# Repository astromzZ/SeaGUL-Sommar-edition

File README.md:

# Seagul - Chalmers undervattensglidare

This repository is for Chalmers underwater glider SEAgul. Here you will find code, instructions and construction files for the glider.

Before handling the glider, make sure to read thorugh the manual. 

The most recent CAD files can be found [here](https://drive.google.com/drive/folders/1H2lXxEGizccBVgk5y8HHm3Ga0hIDHSA2?usp=drive_link).

Contact information:

Oskar Andersson - Oskar.simon.andersson@gmail.com (Programming, CAD)

Peo Gradin - peo.gradin@live.se (Electronics, Programming)

Joel Janson - joeljanson19@gmail.com (Hardware)

Cevin Åström - cevinastrom87@gmail.com (Programming)

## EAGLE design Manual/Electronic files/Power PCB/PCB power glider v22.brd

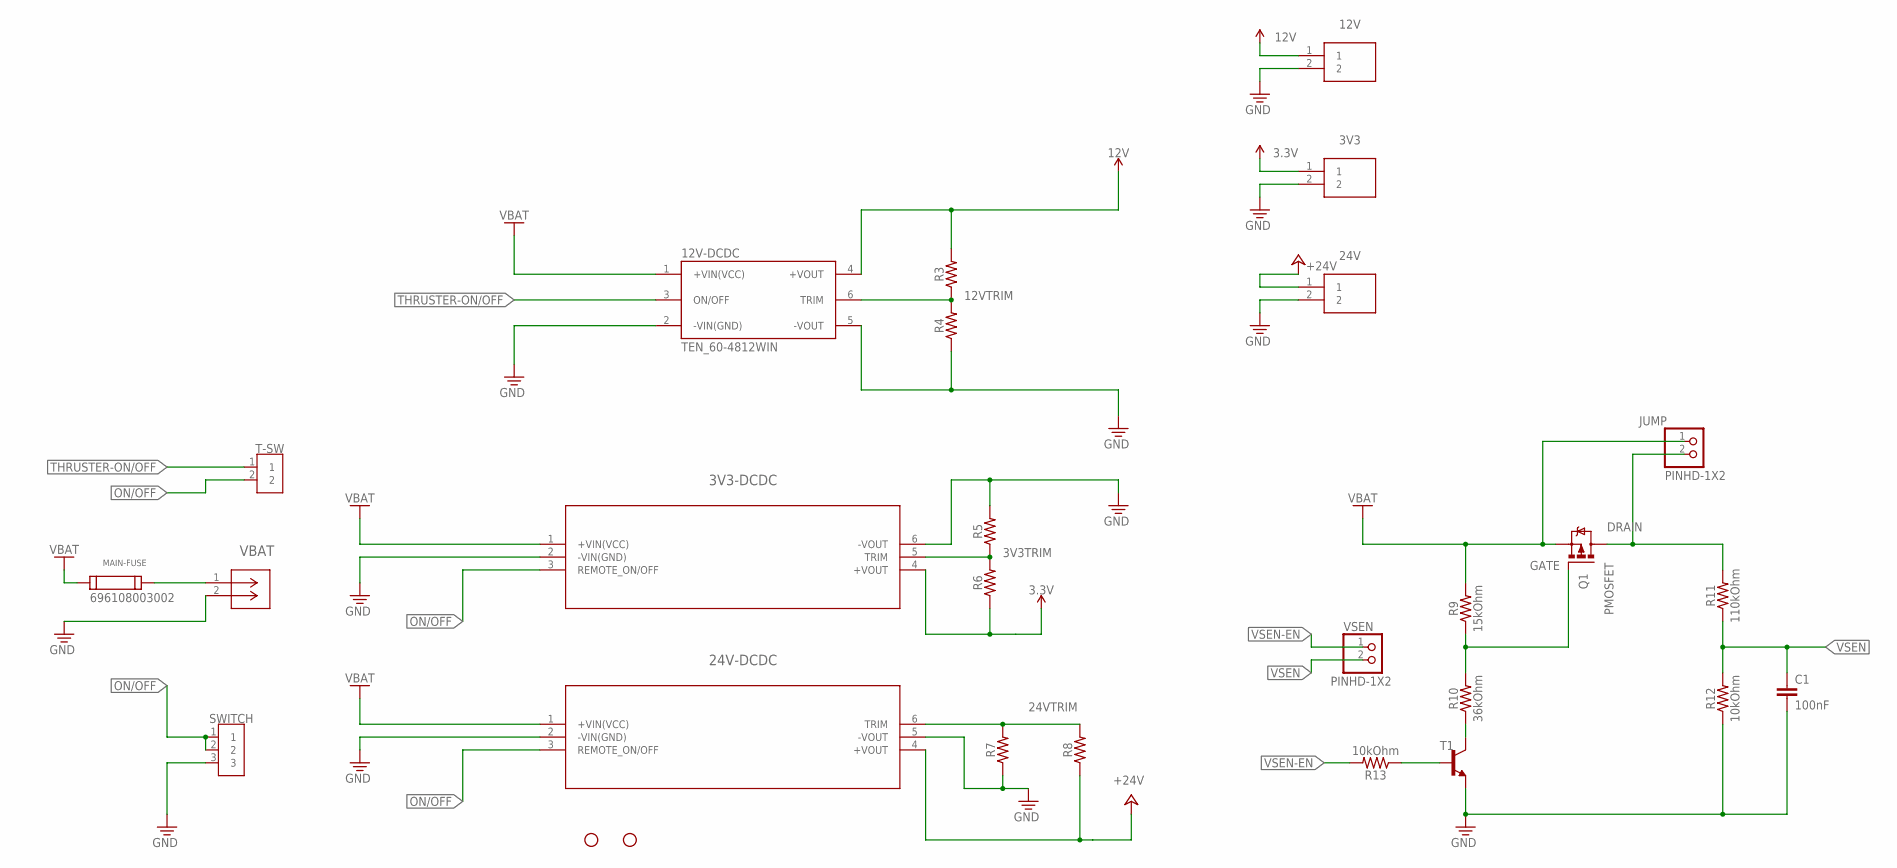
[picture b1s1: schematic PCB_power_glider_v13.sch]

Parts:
3V3, 12V, 24V: CTBP0508_2; CTBP05082
3V3-DCDC: THN_20-4810WIRTHN_20WIR_SINGLE_TRP; THN_20WIR_SINGLE_TRP
12V-DCDC: TEN_60-4812WIN; CONV_TEN_60-4812WIN
24V-DCDC: TEN_60-4815WINTEN_60WIN_TRP; TEN_60WIN_TRP
C1: 100nF; 0603
H1, H4: STAND-OFFTIGHT; STAND-OFF-TIGHT
JUMP: PINHD-1X2; 1X02
MAIN-FUSE: 696108003002
Q1: PMOSFET; SOT23
R3, R4, R5, R6, R7, R8: 0603
R9: 15kOhm; 0603
R10: 36kOhm; 0603
R11: 110kOhm; 0603
R12, R13: 10kOhm; 0603
SWITCH: 2828XX-3282834-3; TERMBLK_254-3N
T1: -NPN-SOT23-EBC; SOT23-EBC
T-SW: 2828XX-2282834-2; TERMBLK_254-2N
VBAT: NC6-P107-02CONN2_1437664-4_TEC; CONN2_1437664-4_TEC
VSEN: PINHD-1X2; 1X02

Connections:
3.3V: 3V3.1, 3V3-DCDC.4 (+VOUT), R6.1
3V3TRIM: 3V3-DCDC.5 (TRIM), R5.1, R6.2
12V: 12V.1, 12V-DCDC.4 (+VOUT), R3.2
12VTRIM: 12V-DCDC.6 (TRIM), R3.1, R4.2
24VTRIM: 24V-DCDC.6 (TRIM), R7.2, R8.2
+24V: 24V.1, 24V-DCDC.4 (+VOUT), R8.1
DRAIN: JUMP.2, Q1.3 (D), R11.2
GATE: Q1.1 (G), R9.1, R10.2
GND: 3V3.2, 3V3-DCDC.2 (-VIN(GND)), 3V3-DCDC.6 (-VOUT), 12V.2, 12V-DCDC.2 (-VIN(GND)), 12V-DCDC.5 (-VOUT), 24V.2, 24V-DCDC.2 (-VIN(GND)), 24V-DCDC.5 (-VOUT), C1.2, R4.1, R5.2, R7.1, R12.1, SWITCH.3, T1.E, VBAT.2
unnamed: MAIN-FUSE.2, VBAT.1
unnamed: R10.1, T1.C
unnamed: R13.1, T1.B
ON/OFF: 3V3-DCDC.3 (REMOTE_ON/OFF), 24V-DCDC.3 (REMOTE_ON/OFF), SWITCH.1, SWITCH.2, T-SW.2
THRUSTER-ON/OFF: 12V-DCDC.3 (ON/OFF), T-SW.1
VBAT: 3V3-DCDC.1 (+VIN(VCC)), 12V-DCDC.1 (+VIN(VCC)), 24V-DCDC.1 (+VIN(VCC)), JUMP.1, MAIN-FUSE.1, Q1.2 (S), R9.2
VSEN: C1.1, R11.1, R12.2, VSEN.2
VSEN-EN: R13.2, VSEN.1

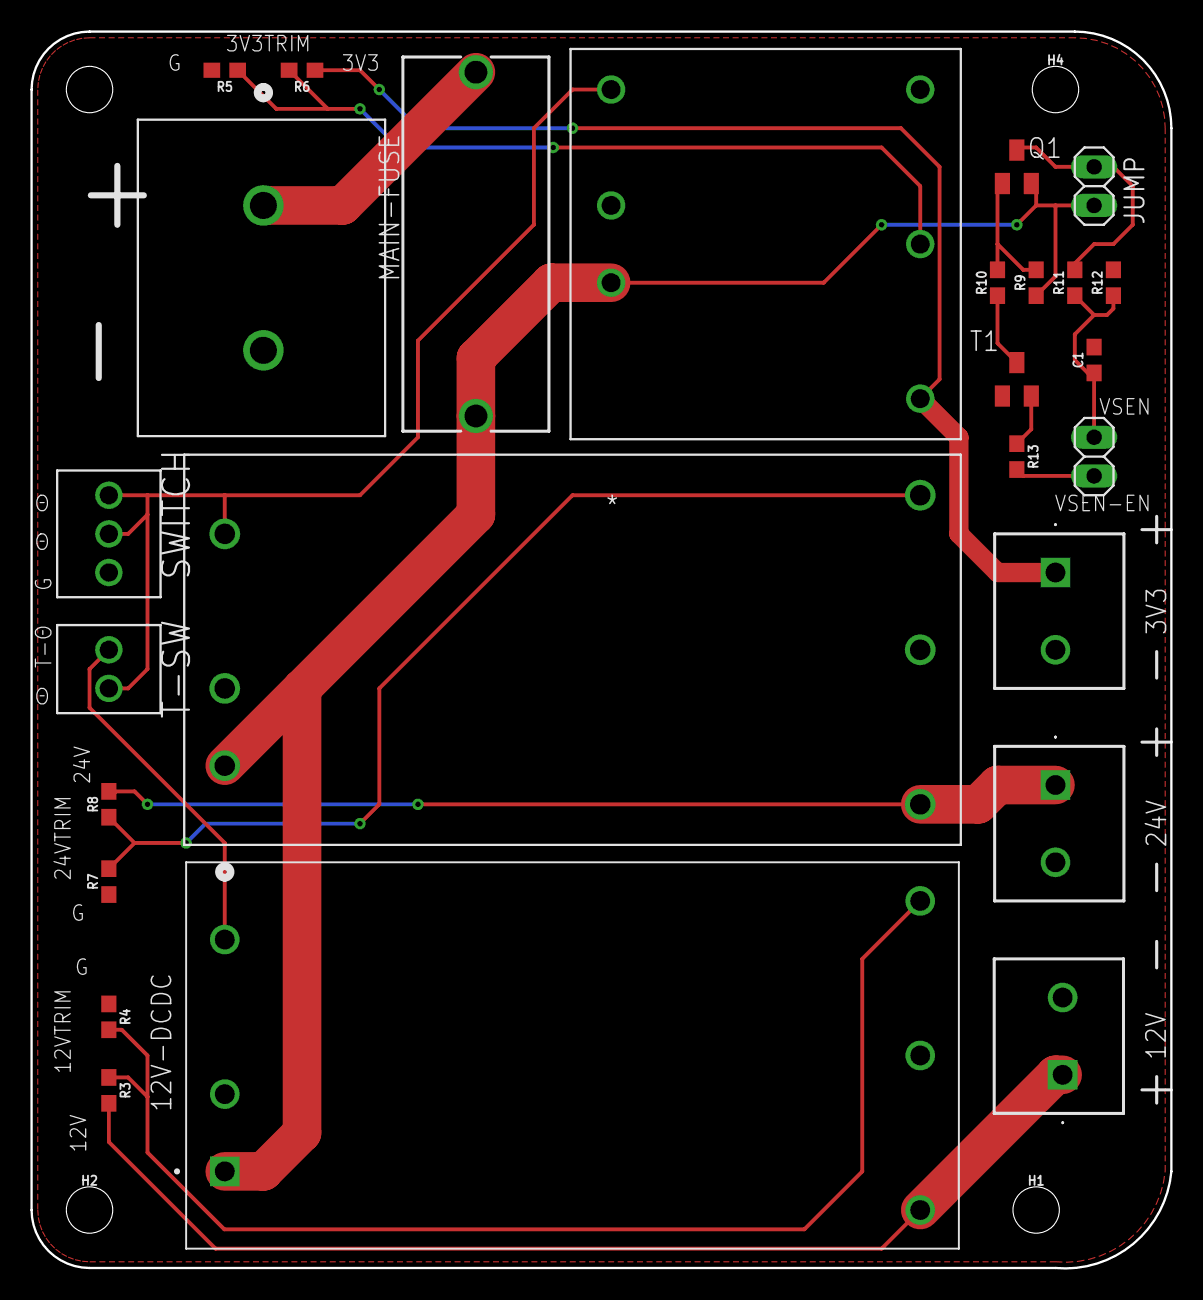
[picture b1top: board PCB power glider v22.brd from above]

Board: 2 copper layers, 74.9 x 81.3 mm, 30 parts (0 on the bottom side), 17 nets.

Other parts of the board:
H2, H3: STAND-OFFTIGHT; STAND-OFF-TIGHT

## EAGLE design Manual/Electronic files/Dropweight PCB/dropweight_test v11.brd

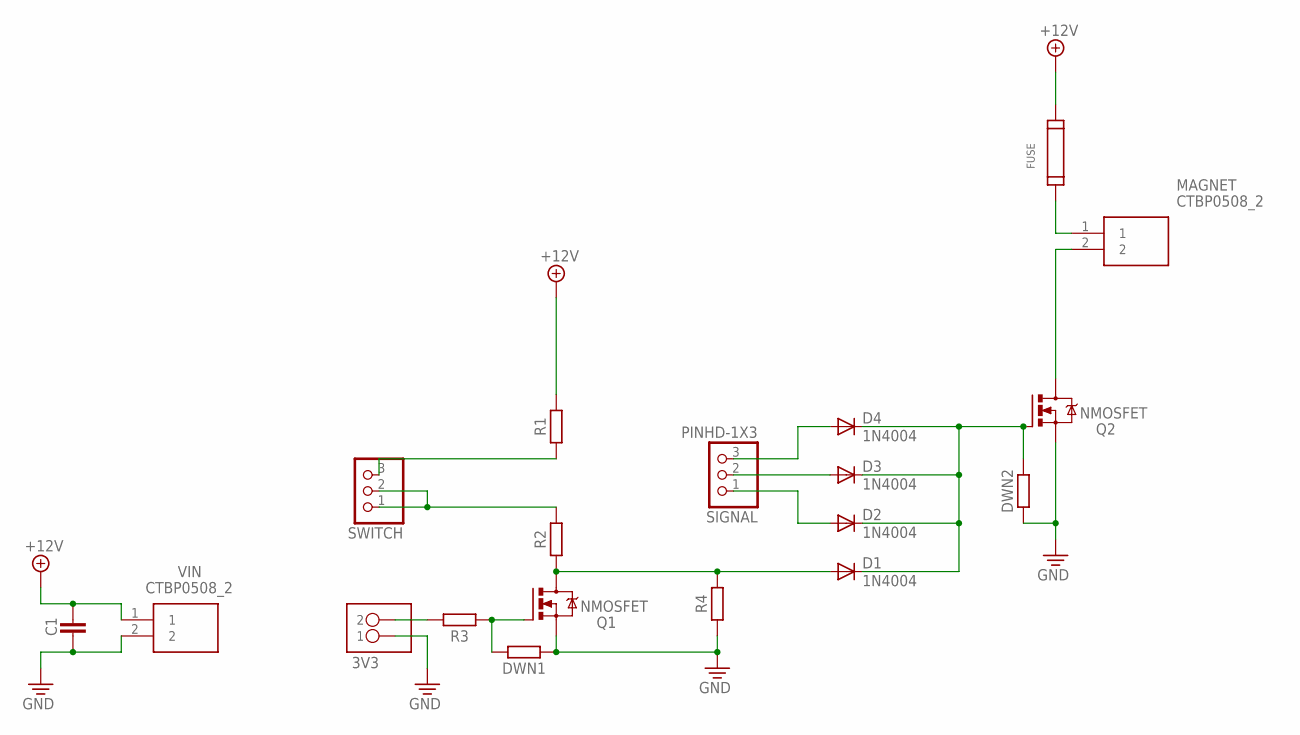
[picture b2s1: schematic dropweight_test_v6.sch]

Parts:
3V3: PINHD-1X02_1X02M; 1X02
C1: CAPACITORCERAMIC-2.54MM; CAP-THRU-2.54MM
D1, D2, D3, D4: 1N4004; DO41-10
DWN1, DWN2: RESISTOR-BACKUP_AXIAL-10.16MM-PITCH; RESAD1016W63L850D250B
FUSE: 696108003002
MAGNET: CTBP0508_2; CTBP05082
Q1, Q2: NMOSFET; TO220BV
R1, R2, R3, R4: RESISTOR-BACKUP_AXIAL-10.16MM-PITCH; RESAD1016W63L850D250B
SIGNAL: PINHD-1X3; 1X03
SWITCH: PINHD-1X3; 1X03
VIN: CTBP0508_2; CTBP05082

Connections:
3V3: 3V3.2, R3.2
+12V: C1.1, FUSE.2, R1.2, VIN.1
GND: 3V3.1, C1.2, DWN1.1, DWN2.1, Q1.S, Q2.S, R4.1, VIN.2
unnamed: R1.1, SWITCH.3
unnamed: R2.2, SWITCH.1, SWITCH.2
unnamed: D1.A, Q1.D, R2.1, R4.2
unnamed: DWN1.2, Q1.G, R3.1
unnamed: MAGNET.2, Q2.D
unnamed: D3.A, SIGNAL.2
unnamed: D4.A, SIGNAL.3
unnamed: D2.A, SIGNAL.1
unnamed: FUSE.1, MAGNET.1
unnamed: D1.C, D2.C, D3.C, D4.C, DWN2.2, Q2.G

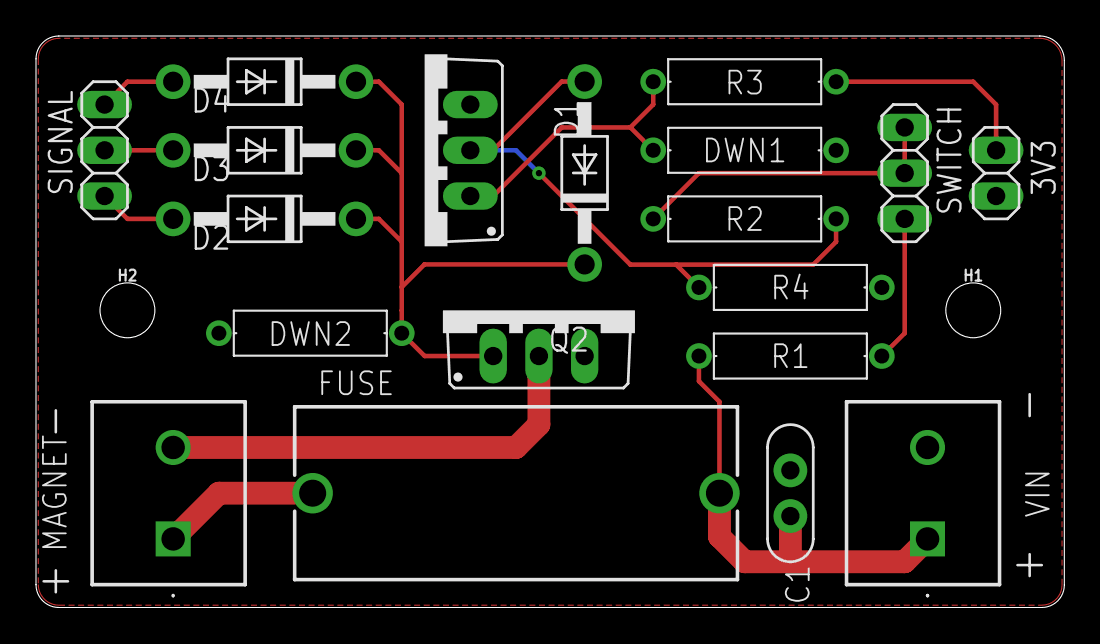
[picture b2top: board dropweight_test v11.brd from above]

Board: 2 copper layers, 57.1 x 31.8 mm, 21 parts (0 on the bottom side), 13 nets.

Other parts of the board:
H1, H2: STAND-OFFTIGHT; STAND-OFF-TIGHT

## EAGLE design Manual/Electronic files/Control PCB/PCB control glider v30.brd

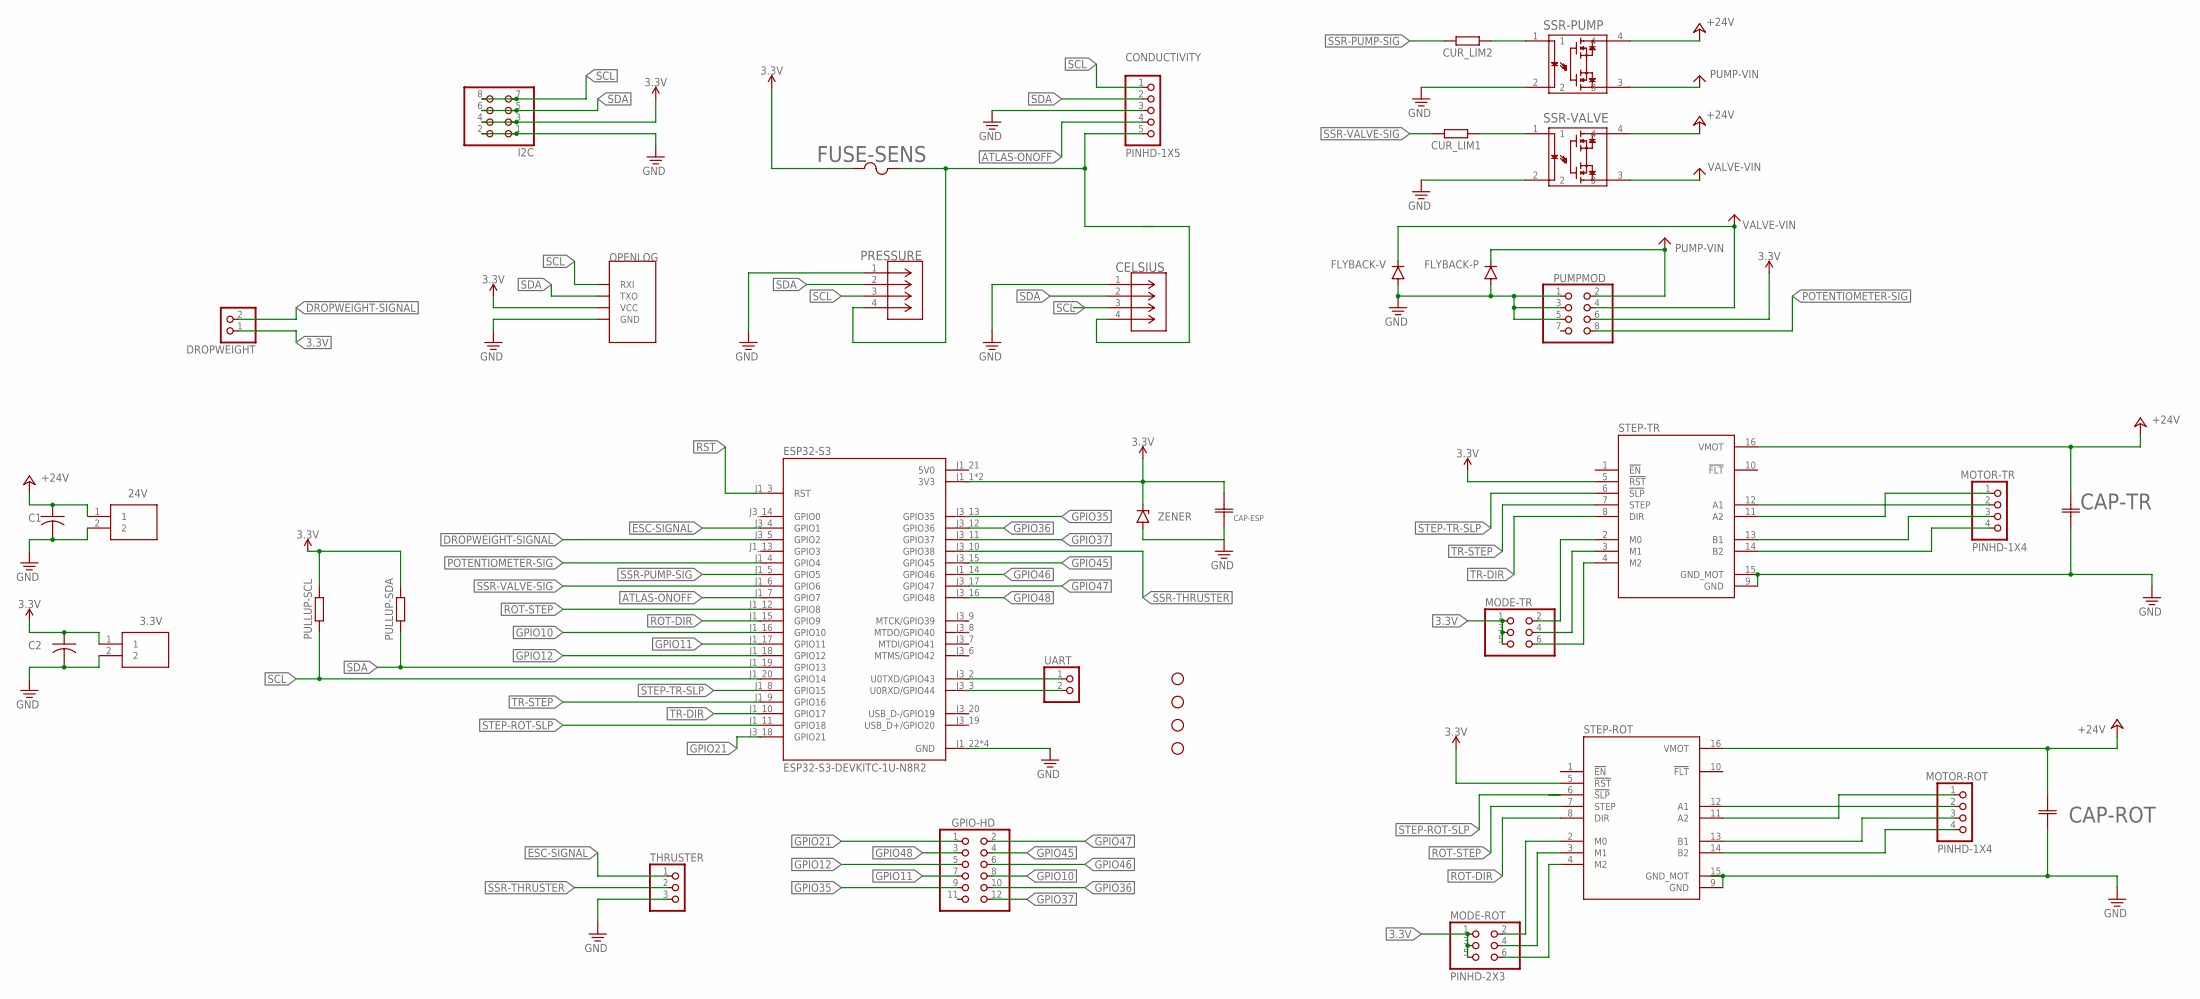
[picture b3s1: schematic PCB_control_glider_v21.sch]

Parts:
3.3V, 24V: CTBP0508_2; CTBP05082
C1, C2: ECA-1HM100; CAP_RADIAL_2MM
CAP-ESP: EEUHD1H101BCAP_PAN_8X11.5_PAN; CAP_PAN_8X11.5_PAN
CAP-ROT: EEUHD1H101BCAP_PAN_8X11.5_PAN; CAP_PAN_8X11.5_PAN
CAP-TR: EEUHD1H101BCAP_PAN_8X11.5_PAN; CAP_PAN_8X11.5_PAN
CELSIUS: BM04B-GHS-TBTCONN_BM04B-GHS-TBT_JST; CONN_BM04B-GHS-TBT_JST
CONDUCTIVITY: PINHD-1X5; 1X05
CUR_LIM1, CUR_LIM2: RESISTOR-BACKUP_AXIAL-10.16MM-PITCH; RESAD1016W63L850D250B
DROPWEIGHT: PINHD-1X2; 1X02
ESP32-S3: ESP32-S3-DEVKITC-1U-N8R2; XCVR_ESP32-S3-DEVKITC-1U-N8R2
FLYBACK-P: 1N4004; DO-41
FLYBACK-V: 1N4004; DO-41
FUSE-SENS: LVR033KFUS_LVR033_TYCO_TYC; FUS_LVR033_TYCO_TYC
GPIO-HD: PINHD-2X6; 2X06
H1, H2, H3, H4: STAND-OFFTIGHT; STAND-OFF-TIGHT
I2C: PINHD-2X4; 2X04
MODE-ROT: PINHD-2X3; 2X03
MODE-TR: PINHD-2X3; 2X03
MOTOR-ROT: PINHD-1X4; 1X04
MOTOR-TR: PINHD-1X4; 1X04
PRESSURE: BM04B-GHS-TBTCONN_BM04B-GHS-TBT_JST; CONN_BM04B-GHS-TBT_JST
PULLUP-SCL: RESISTOR-BACKUP_AXIAL-10.16MM-PITCH; RESAD1016W63L850D250B
PULLUP-SDA: RESISTOR-BACKUP_AXIAL-10.16MM-PITCH; RESAD1016W63L850D250B
PUMPMOD: PINHD-2X4; 2X04
QWIIC-OPENLOG: OPENLOG
SSR-PUMP: G3VM-61ARA-DIP4_THD_OMR; A-DIP4_THD_OMR
SSR-VALVE: G3VM-61ARA-DIP4_THD_OMR; A-DIP4_THD_OMR
STEP-ROT: DRV8825_STEPPER_MOTOR_DRIVER_CARRIER; IC_DRV8825_STEPPER_MOTOR_DRIVER_CARRIER
STEP-TR: DRV8825_STEPPER_MOTOR_DRIVER_CARRIER; IC_DRV8825_STEPPER_MOTOR_DRIVER_CARRIER
THRUSTER: PINHD-1X3; 1X03
UART: PINHD-1X2; 1X02
ZENER: ZENER_DIODE-AXIAL; DIODE-AXIAL

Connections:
3.3V: 3.3V.1, C2.1, CAP-ESP.1, DROPWEIGHT.1, ESP32-S3.J1_1 (3V3), ESP32-S3.J1_2 (3V3), FUSE-SENS.1, I2C.3, I2C.4, MODE-ROT.1, MODE-ROT.3, MODE-ROT.5, MODE-TR.1, MODE-TR.3, MODE-TR.5, PULLUP-SCL.2, PULLUP-SDA.2, PUMPMOD.6, QWIIC-OPENLOG.VCC, STEP-ROT.5 (!RST), STEP-TR.5 (!RST), ZENER.2 (C)
5V0: ESP32-S3.J1_21 (5V0)
+24V: 24V.1, C1.1, CAP-ROT.1, CAP-TR.1, SSR-PUMP.4, SSR-VALVE.4, STEP-ROT.16 (VMOT), STEP-TR.16 (VMOT)
ATLAS-ONOFF: CONDUCTIVITY.4, ESP32-S3.J1_7 (GPIO7)
DROPWEIGHT-SIGNAL: DROPWEIGHT.2, ESP32-S3.J3_5 (GPIO2)
ESC-SIGNAL: ESP32-S3.J3_4 (GPIO1), THRUSTER.1
GND: 3.3V.2, 24V.2, C1.2, C2.2, CAP-ESP.2, CAP-ROT.2, CAP-TR.2, CELSIUS.1, CONDUCTIVITY.3, ESP32-S3.J1_22 (GND), ESP32-S3.J3_1 (GND), ESP32-S3.J3_21 (GND), ESP32-S3.J3_22 (GND), FLYBACK-P.A, FLYBACK-V.A, I2C.1, I2C.2, PRESSURE.1, PUMPMOD.1, PUMPMOD.3, PUMPMOD.5, QWIIC-OPENLOG.GND, SSR-PUMP.2, SSR-VALVE.2, STEP-ROT.9 (GND), STEP-ROT.15 (GND_MOT), STEP-TR.9 (GND), STEP-TR.15 (GND_MOT), THRUSTER.3, ZENER.1 (A)
GPIO10: ESP32-S3.J1_16 (GPIO10), GPIO-HD.8
GPIO11: ESP32-S3.J1_17 (GPIO11), GPIO-HD.7
GPIO12: ESP32-S3.J1_18 (GPIO12), GPIO-HD.5
GPIO21: ESP32-S3.J3_18 (GPIO21), GPIO-HD.1
GPIO35: ESP32-S3.J3_13 (GPIO35), GPIO-HD.9
GPIO36: ESP32-S3.J3_12 (GPIO36), GPIO-HD.10
GPIO37: ESP32-S3.J3_11 (GPIO37), GPIO-HD.12
GPIO45: ESP32-S3.J3_15 (GPIO45), GPIO-HD.4
GPIO46: ESP32-S3.J1_14 (GPIO46), GPIO-HD.6
GPIO47: ESP32-S3.J3_17 (GPIO47), GPIO-HD.2
GPIO48: ESP32-S3.J3_16 (GPIO48), GPIO-HD.3
unnamed: ESP32-S3.J3_2 (U0TXD/GPIO43), UART.1
unnamed: ESP32-S3.J3_3 (U0RXD/GPIO44), UART.2
unnamed: MODE-TR.2, STEP-TR.2 (M0)
unnamed: MODE-TR.4, STEP-TR.3 (M1)
unnamed: MODE-TR.6, STEP-TR.4 (M2)
unnamed: CELSIUS.4, CONDUCTIVITY.5, FUSE-SENS.2, PRESSURE.4
unnamed: MODE-ROT.2, STEP-ROT.2 (M0)
unnamed: MODE-ROT.6, STEP-ROT.4 (M2)
unnamed: MODE-ROT.4, STEP-ROT.3 (M1)
unnamed: CUR_LIM2.1, SSR-PUMP.1
unnamed: CUR_LIM1.1, SSR-VALVE.1
POTENTIOMETER-SIG: ESP32-S3.J1_4 (GPIO4), PUMPMOD.8
PUMP-VIN: FLYBACK-P.C, PUMPMOD.2, SSR-PUMP.3
R-A1: MOTOR-ROT.2, STEP-ROT.12 (A1)
R-A2: MOTOR-ROT.1, STEP-ROT.11 (A2)
R-B1: MOTOR-ROT.3, STEP-ROT.13 (B1)
R-B2: MOTOR-ROT.4, STEP-ROT.14 (B2)
ROT-DIR: ESP32-S3.J1_15 (GPIO9), STEP-ROT.8 (DIR)
ROT-STEP: ESP32-S3.J1_12 (GPIO8), STEP-ROT.7 (STEP)
RST: ESP32-S3.J1_3 (RST)
SCL: CELSIUS.3, CONDUCTIVITY.1, ESP32-S3.J1_20 (GPIO14), I2C.7, I2C.8, PRESSURE.3, PULLUP-SCL.1, QWIIC-OPENLOG.RXI
SDA: CELSIUS.2, CONDUCTIVITY.2, ESP32-S3.J1_19 (GPIO13), I2C.5, I2C.6, PRESSURE.2, PULLUP-SDA.1, QWIIC-OPENLOG.TXO
SSR-PUMP-SIG: CUR_LIM2.2, ESP32-S3.J1_5 (GPIO5)
SSR-THRUSTER: ESP32-S3.J3_10 (GPIO38), THRUSTER.2
SSR-VALVE-SIG: CUR_LIM1.2, ESP32-S3.J1_6 (GPIO6)
STEP-ROT-SLP: ESP32-S3.J1_11 (GPIO18), STEP-ROT.6 (!SLP)
STEP-TR-SLP: ESP32-S3.J1_8 (GPIO15), STEP-TR.6 (!SLP)
T-A1: MOTOR-TR.2, STEP-TR.12 (A1)
T-A2: MOTOR-TR.1, STEP-TR.11 (A2)
T-B1: MOTOR-TR.3, STEP-TR.13 (B1)
T-B2: MOTOR-TR.4, STEP-TR.14 (B2)
TR-DIR: ESP32-S3.J1_10 (GPIO17), STEP-TR.8 (DIR)
TR-STEP: ESP32-S3.J1_9 (GPIO16), STEP-TR.7 (STEP)
VALVE-VIN: FLYBACK-V.C, PUMPMOD.4, SSR-VALVE.3

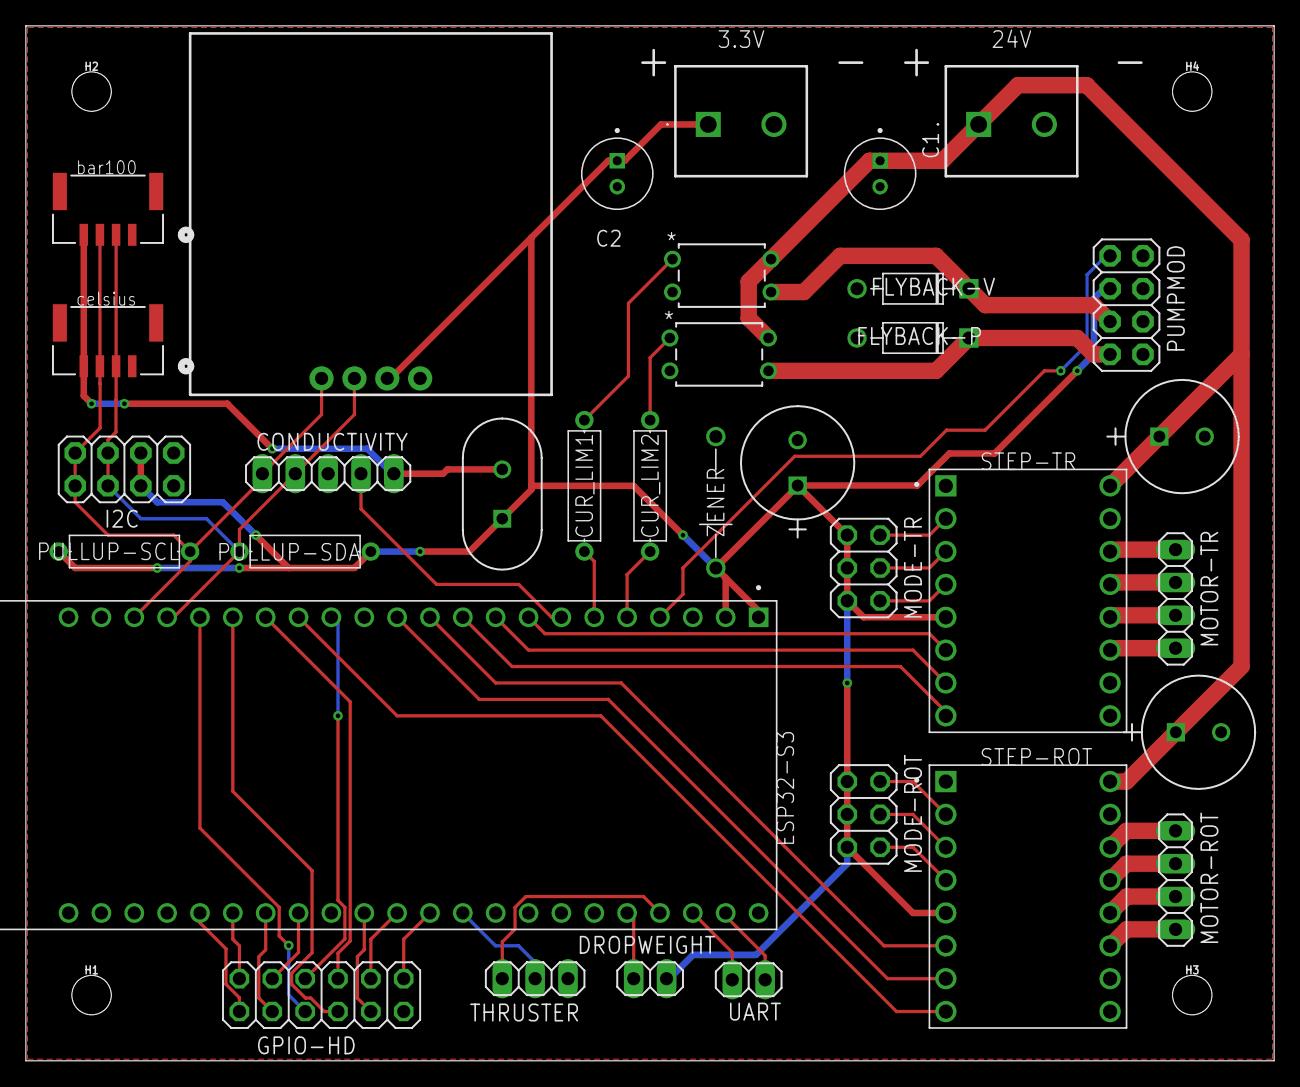
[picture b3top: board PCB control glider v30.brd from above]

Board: 2 copper layers, 96.5 x 80.0 mm, 38 parts (0 on the bottom side), 50 nets.

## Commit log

2024-06-03 Lagt in mappar för koden 2023 och för huvudprogrammet
2024-06-04 Bytt lite namn
2024-06-04 Allmän organisering
2024-06-04 Lagt in lite tester från senast
2024-06-04 Skapat skiss för nytt huvudprogram
2024-06-05 Nya tester genomförda, ytterligare organisering
2024-06-10 Lagt till tester
2024-06-13 Fler tester
2024-06-25 Lite WiFi-tester gjorda
2024-06-26 Fler WiFi-tester
2024-06-27 Manual
2024-06-27 Nya WiFi-tester och uppdaterat huvudprogram
2024-07-01 WiFi-förbättringar, börjat på nytt huvudprogram
2024-07-02 Lade till hello world
2024-07-05 Kalibrering av magnetometer
2024-07-05 plotting
2024-07-05 DATA
2024-07-09 Kalibreringstester
2024-07-09 mer kalibrering
2024-07-15 Lade till map
2024-07-15 smt random
2024-07-19 ny test
2024-07-23 atlas command kod UART och I2C
2024-07-24 Kommunikation AGT ESP
2024-07-24 test orientering
2024-07-24 Början agt
2024-07-25 monterat test 1
2024-07-25 nytt namn
2024-07-31 Tester kommunikation agt och esp
2024-08-01 Fler tester agt esp
2024-08-02 stegmotortester
2024-08-05 random push
2024-08-06 Stegmotorer
2024-08-06 Stegmotorer och utökad testkod
2024-08-08 Rename Skärmbild 2024-07-25 101453.png to ESP-pinout.png
2024-08-08 hemsida, potentiometer
2024-08-08 Elektronik-manual
2024-08-09 fix punkt potentiometer
2024-08-09 added diving logic
2024-08-09 Electronics manual
2024-08-12 surface
2024-08-12 hemsida
2024-08-12 Made AGT code in void functions instead of case structure
2024-08-13 AGT kod
2024-08-13 AGT code
    This code for AGT worked to the point that when unconnected to the ESP, it went to the pickup case and retreived GNSS position succesfully and transmitted an iridium message succesfully. GNSS was of 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
2024-08-14 fixed receive message
2024-08-14 added surface communication agt
2024-08-14 surfacebutton
2024-08-15 Rename 0.1 Instruktioner.md to 0.1 Instructions.md
2024-08-15 adde manual
2024-08-15 Manual for programming
2024-08-15 mover programming instructions
2024-08-15 changed name of programming
2024-08-15 moved around some folders
2024-08-15 moved around some more
2024-08-15 minor changes
2024-08-16 Cleaned up
2024-08-16 added wifi isntructions
2024-09-15 added bornö files
2024-09-15 blandade test
2024-09-27 ny bornö fil
2024-09-27 tog bort fake depth
2024-09-27 new file
2024-09-28 new bornö code
2024-09-28 added median depth
2024-09-28 Add files via upload
    'pitch', 'roll', 'yaw', 'depth', 'medianDepth', 'pressure', 'conductivity', 'temperature', 'potentiometer', 'medPot', 'state'
2025-02-20 contact information
2025-02-25 Uploaded some files

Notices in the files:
parts and their libraries:
OpenLog qwiic: Licensing: Creative Commons ShareAlike 4.0 International - https://creativecommons.org/licenses/by-sa/4.0
COPYRIGHT: Copyright (C) 2024 Ultra Librarian. All rights reserved.
Wurth_Connectors_WR-FSH: Copyright: Würth Elektronik
